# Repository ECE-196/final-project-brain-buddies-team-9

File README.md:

#UCSD
# ECE 196 Final Project
## Melissa De La Cruz, Gizelle Mendoza, Dustin Miller

Welcome to our final project for ECE 196 at UCSD. Key items are our poster and website.

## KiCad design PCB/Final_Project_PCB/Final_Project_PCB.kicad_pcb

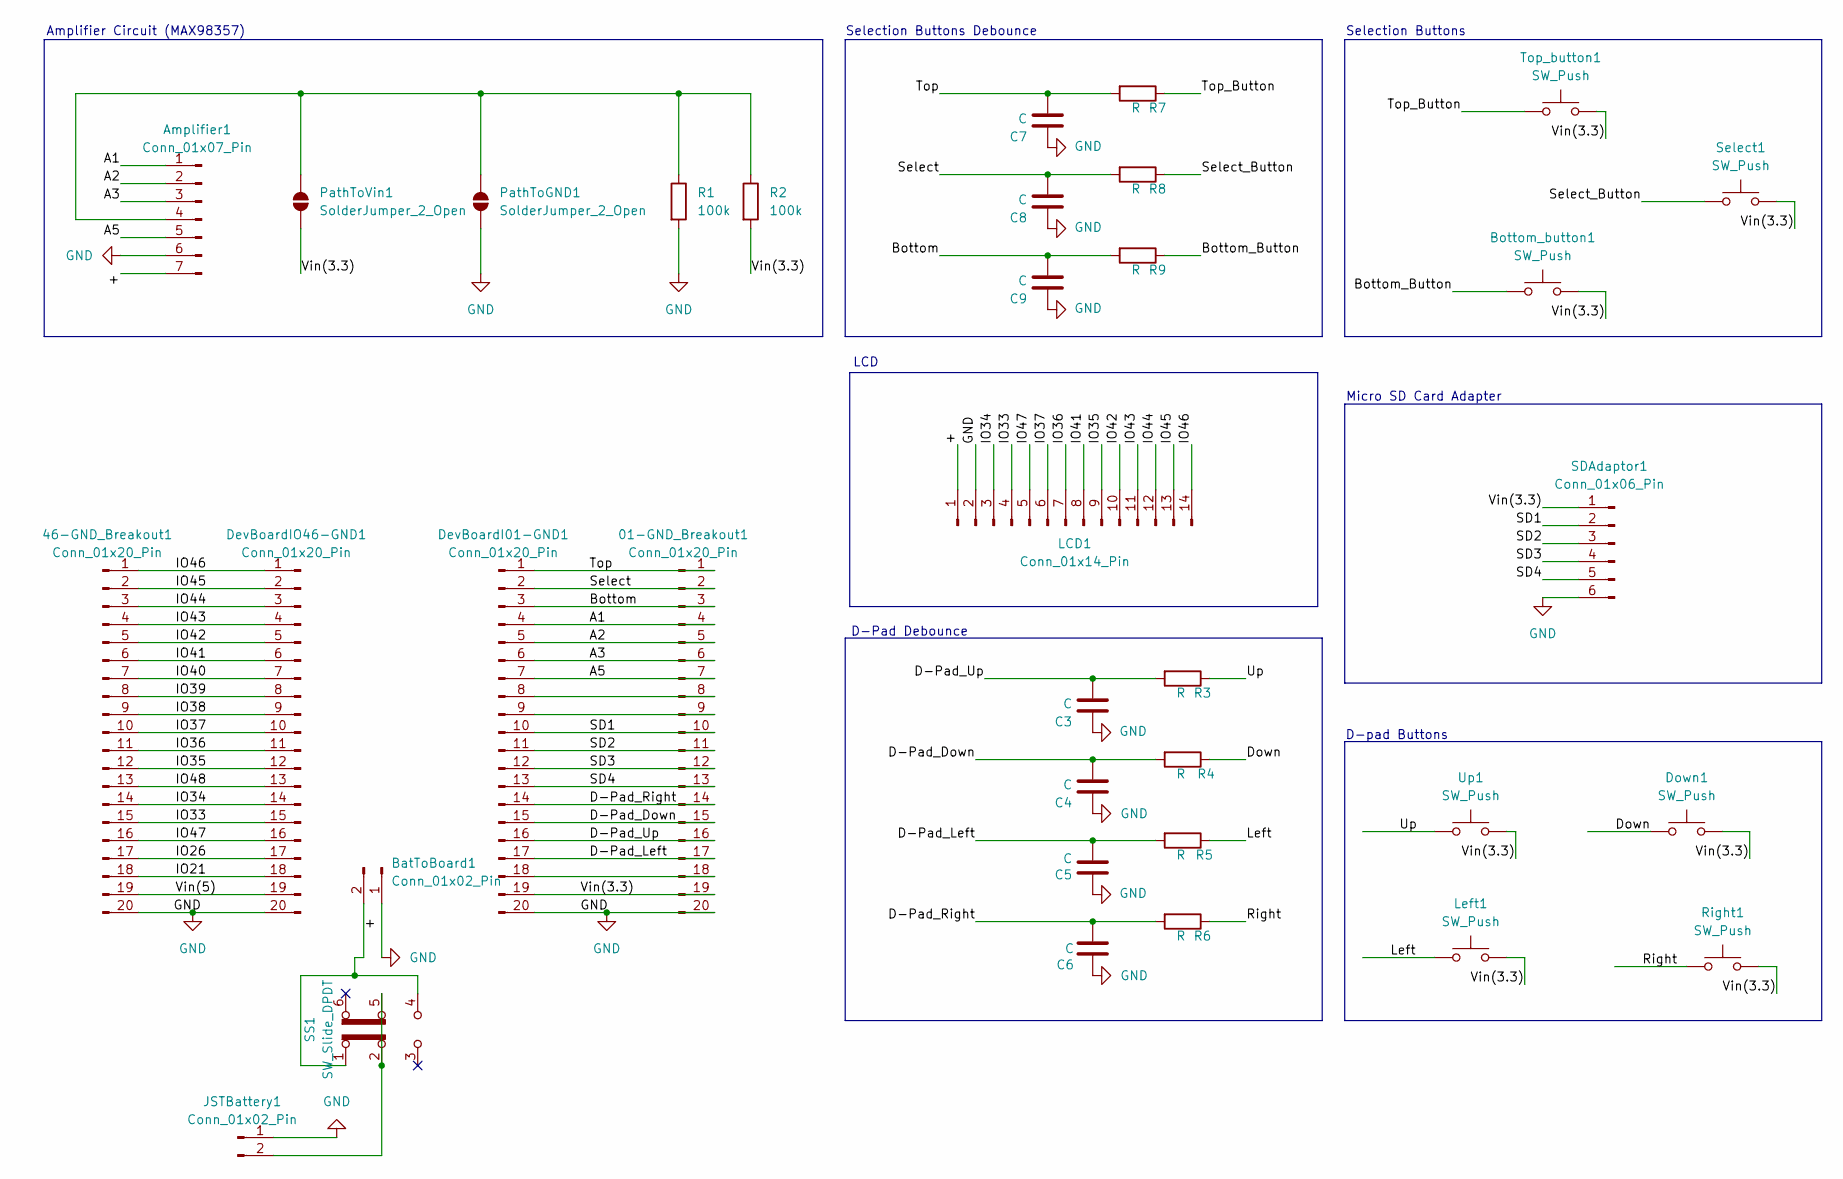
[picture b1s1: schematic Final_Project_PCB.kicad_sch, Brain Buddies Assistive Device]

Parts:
01-GND_Breakout1, 46-GND_Breakout1: Conn_01x20_Pin; PinHeader_1x20_P2.54mm_Vertical
Amplifier1: Conn_01x07_Pin; PinHeader_1x07_P2.54mm_Vertical
BatToBoard1: Conn_01x02_Pin; PinHeader_1x02_P2.54mm_Vertical
Bottom_button1: SW_Push; SW_SPST_PTS810
C3, C4, C5, C6, C7, C8, C9: C; C_0805_2012Metric_Pad1.18x1.45mm_HandSolder
DevBoardI01-GND1: Conn_01x20_Pin; PinHeader_1x20_P2.54mm_Vertical
DevBoardIO46-GND1: Conn_01x20_Pin; PinHeader_1x20_P2.54mm_Vertical
Down1: SW_Push; SW_SPST_PTS810
JSTBattery1: Conn_01x02_Pin; JST_PH_S2B-PH-K_1x02_P2.00mm_Horizontal
LCD1: Conn_01x14_Pin; PinHeader_1x14_P2.54mm_Vertical
Left1: SW_Push; SW_SPST_PTS810
PathToGND1: SolderJumper_2_Open; SolderJumper-2_P1.3mm_Open_RoundedPad1.0x1.5mm
PathToVin1: SolderJumper_2_Open; SolderJumper-2_P1.3mm_Open_RoundedPad1.0x1.5mm
R1, R2: 100k; R_0805_2012Metric_Pad1.20x1.40mm_HandSolder
R3, R4, R5, R6, R7, R8, R9: R; R_0805_2012Metric_Pad1.20x1.40mm_HandSolder
Right1: SW_Push; SW_SPST_PTS810
SDAdaptor1: Conn_01x06_Pin; PinHeader_1x06_P2.54mm_Vertical
SS1: SW_Slide_DPDT; SW_DPDT_CK_JS202011JCQN
Select1: SW_Push; SW_SPST_PTS810
Top_button1: SW_Push; SW_SPST_PTS810
Up1: SW_Push; SW_SPST_PTS810

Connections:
/+: Amplifier1.7, BatToBoard1.2, LCD1.1, SS1.1 (A), SS1.4 (A)
/A1: 01-GND_Breakout1.4, Amplifier1.1, DevBoardI01-GND1.4
/A2: 01-GND_Breakout1.5, Amplifier1.2, DevBoardI01-GND1.5
/A3: 01-GND_Breakout1.6, Amplifier1.3, DevBoardI01-GND1.6
/A5: 01-GND_Breakout1.7, Amplifier1.5, DevBoardI01-GND1.7
/Bottom: 01-GND_Breakout1.3, C9.1, DevBoardI01-GND1.3, R9.2
/Bottom_Button: Bottom_button1.1, R9.1
/D-Pad_Down: 01-GND_Breakout1.15, C4.1, DevBoardI01-GND1.15, R4.2
/D-Pad_Left: 01-GND_Breakout1.17, C5.1, DevBoardI01-GND1.17, R5.2
/D-Pad_Right: 01-GND_Breakout1.14, C6.1, DevBoardI01-GND1.14, R6.2
/D-Pad_Up: 01-GND_Breakout1.16, C3.1, DevBoardI01-GND1.16, R3.2
/Down: Down1.1, R4.1
/IO21: 46-GND_Breakout1.18, DevBoardIO46-GND1.18
/IO26: 46-GND_Breakout1.17, DevBoardIO46-GND1.17
/IO33: 46-GND_Breakout1.15, DevBoardIO46-GND1.15, LCD1.4
/IO34: 46-GND_Breakout1.14, DevBoardIO46-GND1.14, LCD1.3
/IO35: 46-GND_Breakout1.12, DevBoardIO46-GND1.12, LCD1.9
/IO36: 46-GND_Breakout1.11, DevBoardIO46-GND1.11, LCD1.7
/IO37: 46-GND_Breakout1.10, DevBoardIO46-GND1.10, LCD1.6
/IO38: 46-GND_Breakout1.9, DevBoardIO46-GND1.9
/IO39: 46-GND_Breakout1.8, DevBoardIO46-GND1.8
/IO40: 46-GND_Breakout1.7, DevBoardIO46-GND1.7
/IO41: 46-GND_Breakout1.6, DevBoardIO46-GND1.6, LCD1.8
/IO42: 46-GND_Breakout1.5, DevBoardIO46-GND1.5, LCD1.10
/IO43: 46-GND_Breakout1.4, DevBoardIO46-GND1.4, LCD1.11
/IO44: 46-GND_Breakout1.3, DevBoardIO46-GND1.3, LCD1.12
/IO45: 46-GND_Breakout1.2, DevBoardIO46-GND1.2, LCD1.13
/IO46: 46-GND_Breakout1.1, DevBoardIO46-GND1.1, LCD1.14
/IO47: 46-GND_Breakout1.16, DevBoardIO46-GND1.16, LCD1.5
/IO48: 46-GND_Breakout1.13, DevBoardIO46-GND1.13
/Left: Left1.1, R5.1
/Right: R6.1, Right1.1
/SD1: 01-GND_Breakout1.10, DevBoardI01-GND1.10, SDAdaptor1.2
/SD2: 01-GND_Breakout1.11, DevBoardI01-GND1.11, SDAdaptor1.3
/SD3: 01-GND_Breakout1.12, DevBoardI01-GND1.12, SDAdaptor1.4
/SD4: 01-GND_Breakout1.13, DevBoardI01-GND1.13, SDAdaptor1.5
/Select: 01-GND_Breakout1.2, C8.1, DevBoardI01-GND1.2, R8.2
/Select_Button: R8.1, Select1.1
/Top: 01-GND_Breakout1.1, C7.1, DevBoardI01-GND1.1, R7.2
/Top_Button: R7.1, Top_button1.1
/Up: R3.1, Up1.1
/Vin(3.3): 01-GND_Breakout1.19, Bottom_button1.2, DevBoardI01-GND1.19, Down1.2, Left1.2, PathToVin1.1 (A), R2.2, Right1.2, SDAdaptor1.1, Select1.2, Top_button1.2, Up1.2
/Vin(5): 46-GND_Breakout1.19, DevBoardIO46-GND1.19
GND: 01-GND_Breakout1.20, 46-GND_Breakout1.20, Amplifier1.6, BatToBoard1.1, C3.2, C4.2, C5.2, C6.2, C7.2, C8.2, C9.2, DevBoardI01-GND1.20, DevBoardIO46-GND1.20, JSTBattery1.1, LCD1.2, PathToGND1.1 (A), R1.2, SDAdaptor1.6
unnamed: 01-GND_Breakout1.8, DevBoardI01-GND1.8
unnamed: 01-GND_Breakout1.9, DevBoardI01-GND1.9
unnamed: 01-GND_Breakout1.18, DevBoardI01-GND1.18
unnamed: Amplifier1.4, PathToGND1.2 (B), PathToVin1.2 (B), R1.1, R2.1
unnamed: JSTBattery1.2, SS1.2 (B), SS1.5 (B)

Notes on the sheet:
Micro SD Card Adapter
D-Pad Debounce
LCD
D-pad Buttons
Selection Buttons Debounce
Selection Buttons
Amplifier Circuit (MAX98357)

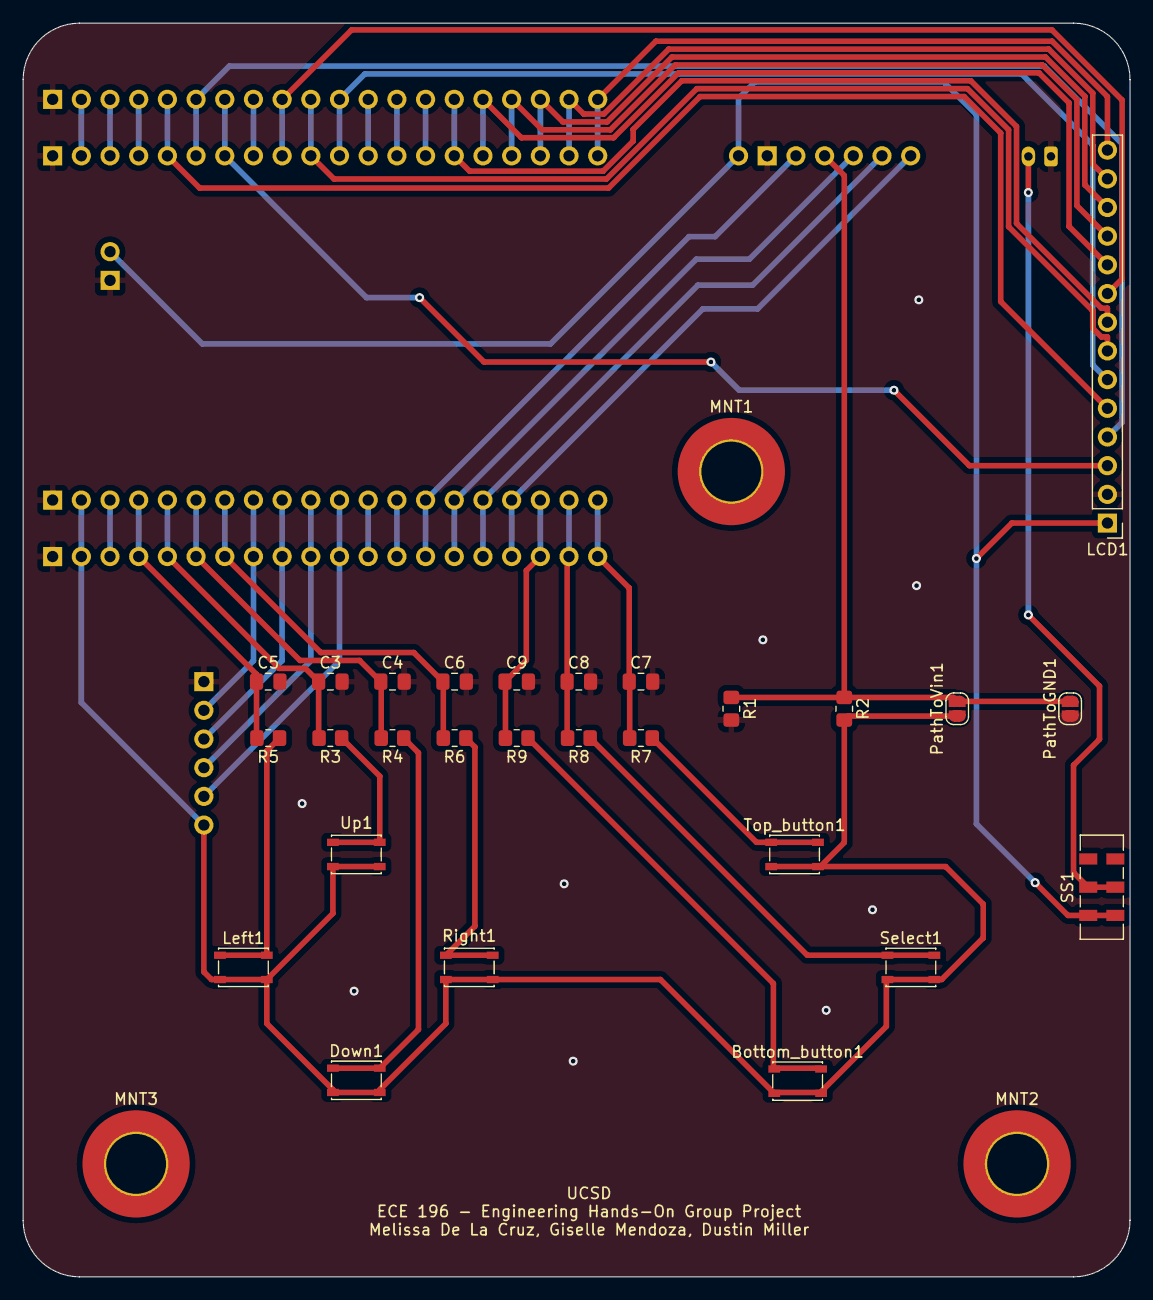
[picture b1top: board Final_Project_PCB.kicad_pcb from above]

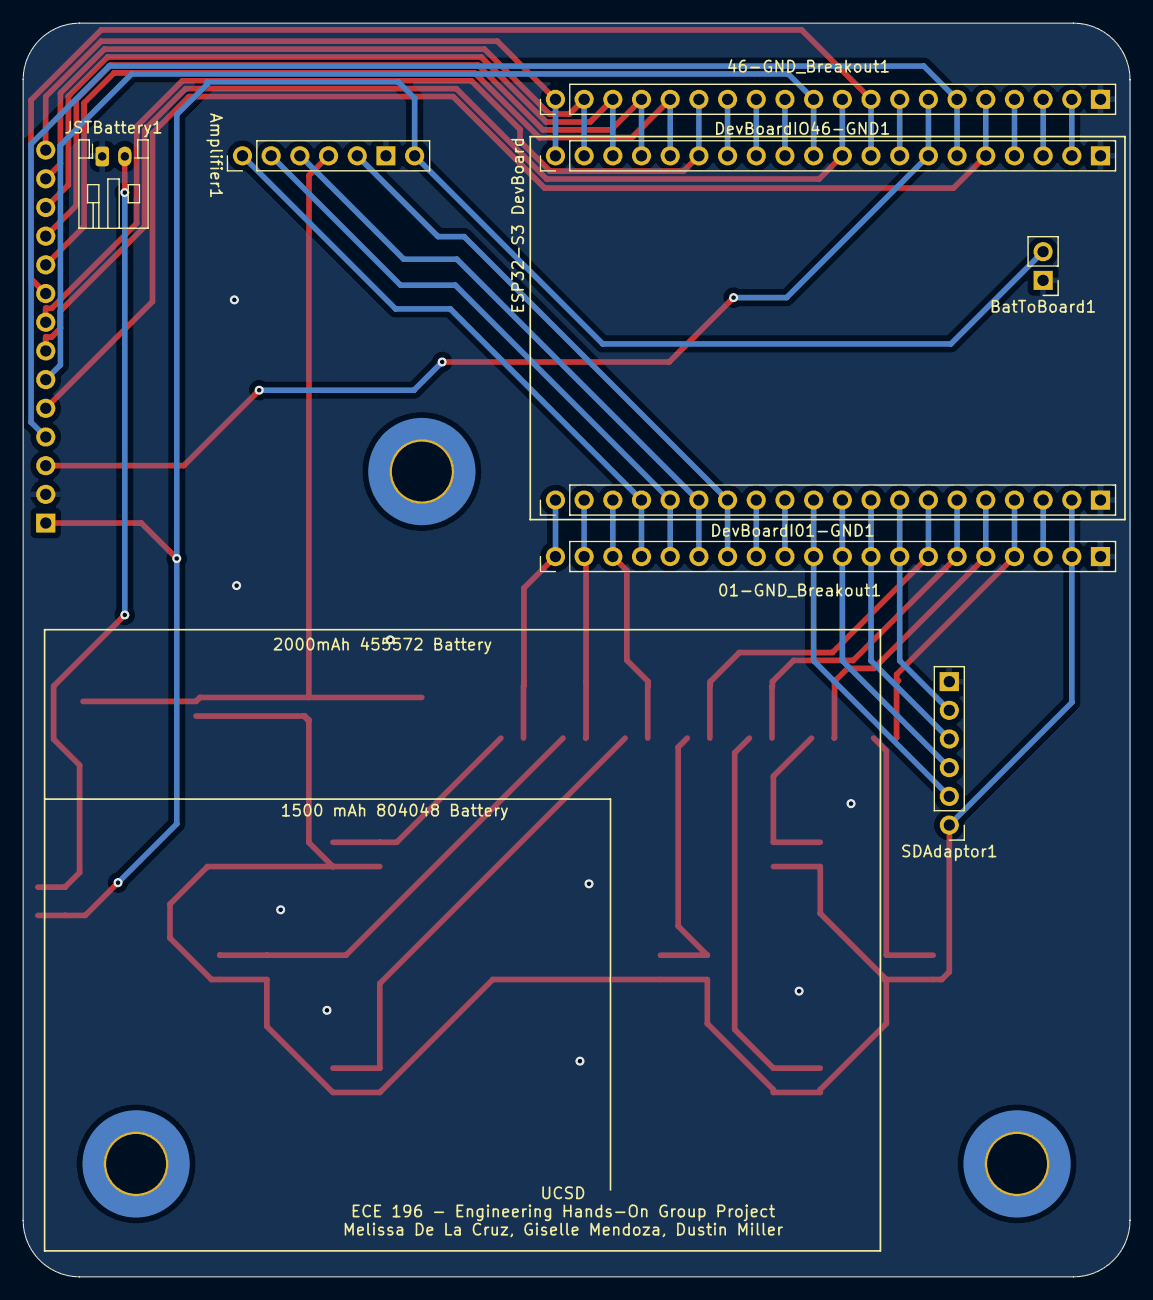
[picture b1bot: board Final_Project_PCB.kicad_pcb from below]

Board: 2 copper layers, 98.0 x 111.0 mm, 38 parts (8 on the bottom side), 49 nets.

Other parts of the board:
MNT1, MNT2, MNT3: MountingHole_5.3mm_M5_ISO7380_Pad_TopBottom

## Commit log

2024-10-29 Create a Kicad Project
2024-10-31 Schematic Finished
2024-10-31 Uploaded Melissa's Sketches
    PCB Sketches
2024-10-31 Kicad Work
2024-11-04 Poster pt1
2024-11-04 current Kicad
2024-11-04 Create website
2024-11-04 Last nov 3 update
2024-11-04 pcb Edits
2024-11-05 Current KiCAD November 4 5PM
2024-11-05 update again
2024-11-05 LDC PCB
2024-11-05 updates againnnn
2024-11-05 Save before filling in front and back planes with copper
2024-11-05 Final PCB Update - Pending Review
2024-11-05 Added a generated BOM
2024-11-05 Generated gerber and drl files
    fixed silk screen overlap
2024-11-17 added sd_test and sd_music test
2024-11-18 Upload Excalidraw Design Files
    These are the exports from excalidraw that the entire team worked on.
2024-11-26 prep for CAD and LCD work
2024-11-26 gitignoring the .DS_Store file
2024-11-26 added cad design
2024-11-26 updated cad design (no buttons)
    add buttons later
2024-11-27 made a folder
2024-11-27 updated cad design
    now has correct orientation of buttons
2024-11-27 code change
2024-11-28 code to test pins on esp32
2024-11-28 final design CAD added
2024-11-30 new button code
2024-11-30 more
2024-12-01 decision button when popup
2024-12-02 updated Porting
2024-12-02 UI color update
2024-12-02 portin updates
2024-12-02 Update to UI homepage pop-up
2024-12-02 change back and done buttons
2024-12-02 update to ui home page
2024-12-02 final changes CAD
2024-12-02 UI updated
2024-12-02 created new container
2024-12-03 lv_conf update
2024-12-03 change font size
2024-12-03 hidden containers
2024-12-03 taskInfo container updated
2024-12-03 fixed size of task page
2024-12-03 visual
2024-12-03 hidden
2024-12-03 change
2024-12-03 racon pic
2024-12-03 racon pt2
2024-12-03 racoonnn
2024-12-03 updatessss
2024-12-03 To do list updated
2024-12-03 updates_separations
2024-12-03 code
2024-12-03 separation of code space
2024-12-03 custom fucntions updated
2024-12-03 includes fixed
2024-12-03 mi nombre es Giselle
2024-12-03 fixed Giselles contvis
2024-12-03 again
2024-12-03 best code out there
2024-12-03 andpersants
2024-12-03 final parts CAD
2024-12-03 updates to porting, wifitime
2024-12-03 fixed alignment of tasks
2024-12-03 ui changes
2024-12-03 UI labels
2024-12-03 Updated code
2024-12-04 fixed EVERYTHING :D
2024-12-04 CODEEEE
2024-12-04 tasks
2024-12-04 final add
2024-12-04 dunnoo
2024-12-04 corrections to bottom part
2024-12-04 compressed final project video
2024-12-04 demo day tasks updated :)
2024-12-05 updates
    added images, organized folders, uploaded final versions of CAD, Poster, etc.
2024-12-05 updates
    more images, added.txt to website, added routine check off list.
2024-12-07 Uploading all documentation created throughout our process.
    The documentation uploaded has mixed authors. I added names to documents with single authors. However, almost everything was a group effort in one way or another.
2024-12-07 Last updates and changes, forgot to push earlier :.)
2024-12-07 added tutorial
